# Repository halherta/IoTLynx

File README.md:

# IoTLynx

A maker-friendly ESP32-C6 development board designed for accessibility and ease of use.

## Overview

IoTLynx is a microcontroller development board based on Espressif's ESP32-C6 microcontroller (ESP32-C6-MINI-1 module). Designed with accessibility in mind, the IoTLynx platform caters to makers, hobbyists, and newcomers to programming and electronics. Though the board supports C programming, it was specifically designed to run MicroPython—a choice that aligns with its philosophy of ease of use. With the MicroPython REPL pre-loaded and ready to run, users can start coding immediately without the hassle of configuring development environments or installing IDEs.

## Features

### Hardware Specifications

**ESP32-C6 (ESP32-C6-MINI-1) Module:**
- **Processor:** RISC-V 32-bit single-core, up to 160 MHz
- **Memory:** 512 KB SRAM, 320 KB ROM, 4 MB embedded flash
- **Wireless:** Wi-Fi 6 (802.11 b/g/n, 2.4 GHz), Bluetooth 5.3 LE
- **GPIO:** 19 programmable GPIOs available on headers
- **Interfaces:** 2× SPI, 2× UART, 1× I2C, 1× I2S
- **Analog:** 7-channel 12-bit SAR ADC
- **PWM:** 6 LED PWM channels
- **USB:** USB 2.0 full-speed (OTG)
- **Other:** Built-in temperature sensor, 7-channel capacitive touch, hardware encryption

**Board Features:**
- **Dimensions:** 58mm × 38mm with rounded edges
- **Power Options:** USB-C or +5V via pin (can use both simultaneously)
- **Voltage Regulator:** Onboard +3.3V regulator
- **Headers:** 2× 14-pin female headers for GPIO access
- **Buttons:** RESET and BOOT pushbuttons
- **LED:** Power-on indicator
- **PCB:** 2-layer design with ground fills for noise immunity
- **Mounting:** M3 mounting holes on all four corners

### Power Consumption
- **Active mode (Wi-Fi):** ~95 mA
- **Modem-sleep:** ~15 mA
- **Light-sleep:** ~3 mA
- **Deep-sleep:** ~7-10 µA

## Pinout

Power can be applied via:
- **USB-C connector** for programming and power
- **+5Vin pin** (5V only) - can be used simultaneously with USB-C
- **+3V3 output** available for powering external components

## Schematic & PCB

The board features a straightforward design with all ESP32-C6-MINI-1 GPIOs (except USB pins) brought out to the headers. View the [full schematic PDF](https://github.com/halherta/IoTLynx/blob/main/IoTLynx.pdf) for complete details.

## Expansion Boards

The IoTLynx is designed to support "Top" boards—add-on boards that attach via the two female header connectors, similar to Arduino shields or Raspberry Pi hats. A KiCad template for creating Top boards is available in the [parts library](https://github.com/halherta/mykicadlibrary).

## Getting Started

### Prerequisites

- [Thonny IDE](https://thonny.org/) (MicroPython IDE)
- [esptool](https://github.com/espressif/esptool) (Espressif's flashing tool)
- [MicroPython firmware for ESP32-C6](https://micropython.org/download/ESP32_GENERIC_C6/)

### Installation

**1. Install Thonny and esptool:**

Via pip (in a Python virtual environment):
```bash
pip install thonny esptool
```

Or via apt (Debian/Ubuntu):
```bash
sudo apt install thonny esptool
```

**2. Find your serial port:**

Linux/Mac:
```bash
ls /dev/tty*
```

Windows (PowerShell):
```powershell
[System.IO.Ports.SerialPort]::getportnames()
```

Look for something like `/dev/ttyUSB0`, `/dev/ttyACM0` (Linux/Mac) or `COM3`, `COM4` (Windows).

**3. Erase the flash:**
```bash
esptool --chip esp32c6 --port /dev/ttyUSB0 erase_flash
```
*Replace `/dev/ttyUSB0` with your actual serial port.*

**4. Flash MicroPython firmware:**
```bash
esptool --chip esp32c6 --port /dev/ttyUSB0 write_flash -z 0x0 ESP32_GENERIC_C6-XXXXXXXX.bin
```
*Replace `ESP32_GENERIC_C6-XXXXXXXX.bin` with your downloaded firmware filename.*

**5. Configure Thonny:**
- Open Thonny
- Go to **Run → Configure Interpreter**
- Select **MicroPython (ESP32)** from the first dropdown
- Select your board's serial port from the second dropdown
- Click **OK**

You should see the MicroPython REPL prompt in the shell window:
```python
MicroPython v1.xx.x on 20xx-xx-xx; ESP32C6 module with ESP32C6
Type "help()" for more information.
>>>
```

Congratulations! You're ready to program your IoTLynx board!

## Repository Contents

- **IoTLynx.kicad_\*** - KiCad project files (schematic, PCB, settings)
- **IoTLynx.pdf** - Schematic in PDF format
- **IoTLynx.svg** - Board illustration
- **production/** - Manufacturing files (gerbers, BOM, etc.)
- **images/** - Documentation images
- **\*-backups/** - KiCad backup files

## Resources

- **Blog Post:** [Detailed IoTLynx writeup](https://hussamtalkstech.com/iotlynx/)
- **Parts Library:** [KiCad parts and Top board template](https://github.com/halherta/mykicadlibrary)
- **ESP32-C6 Datasheet:** [ESP32-C6-MINI-1 documentation](https://documentation.espressif.com/esp32-c6-mini-1_mini-1u_datasheet_en.html)
- **MicroPython Documentation:** [MicroPython for ESP32](https://docs.micropython.org/en/latest/esp32/quickref.html)

## License

This hardware project is open source. Please check the repository for specific license information.

## Contributing

Contributions, issues, and feature requests are welcome! Feel free to check the issues page or submit a pull request.

## Support

For questions, issues, or discussions about the IoTLynx board:
- Open an issue on this repository
- Visit the [blog post](https://hussamtalkstech.com/iotlynx/) for additional details

## Author

Created by [halherta](https://github.com/halherta)

---

**Note:** While the ESP32-C6 supports Zigbee, Thread, 6LoWPAN, and Matter protocols, these features are not currently available through MicroPython.

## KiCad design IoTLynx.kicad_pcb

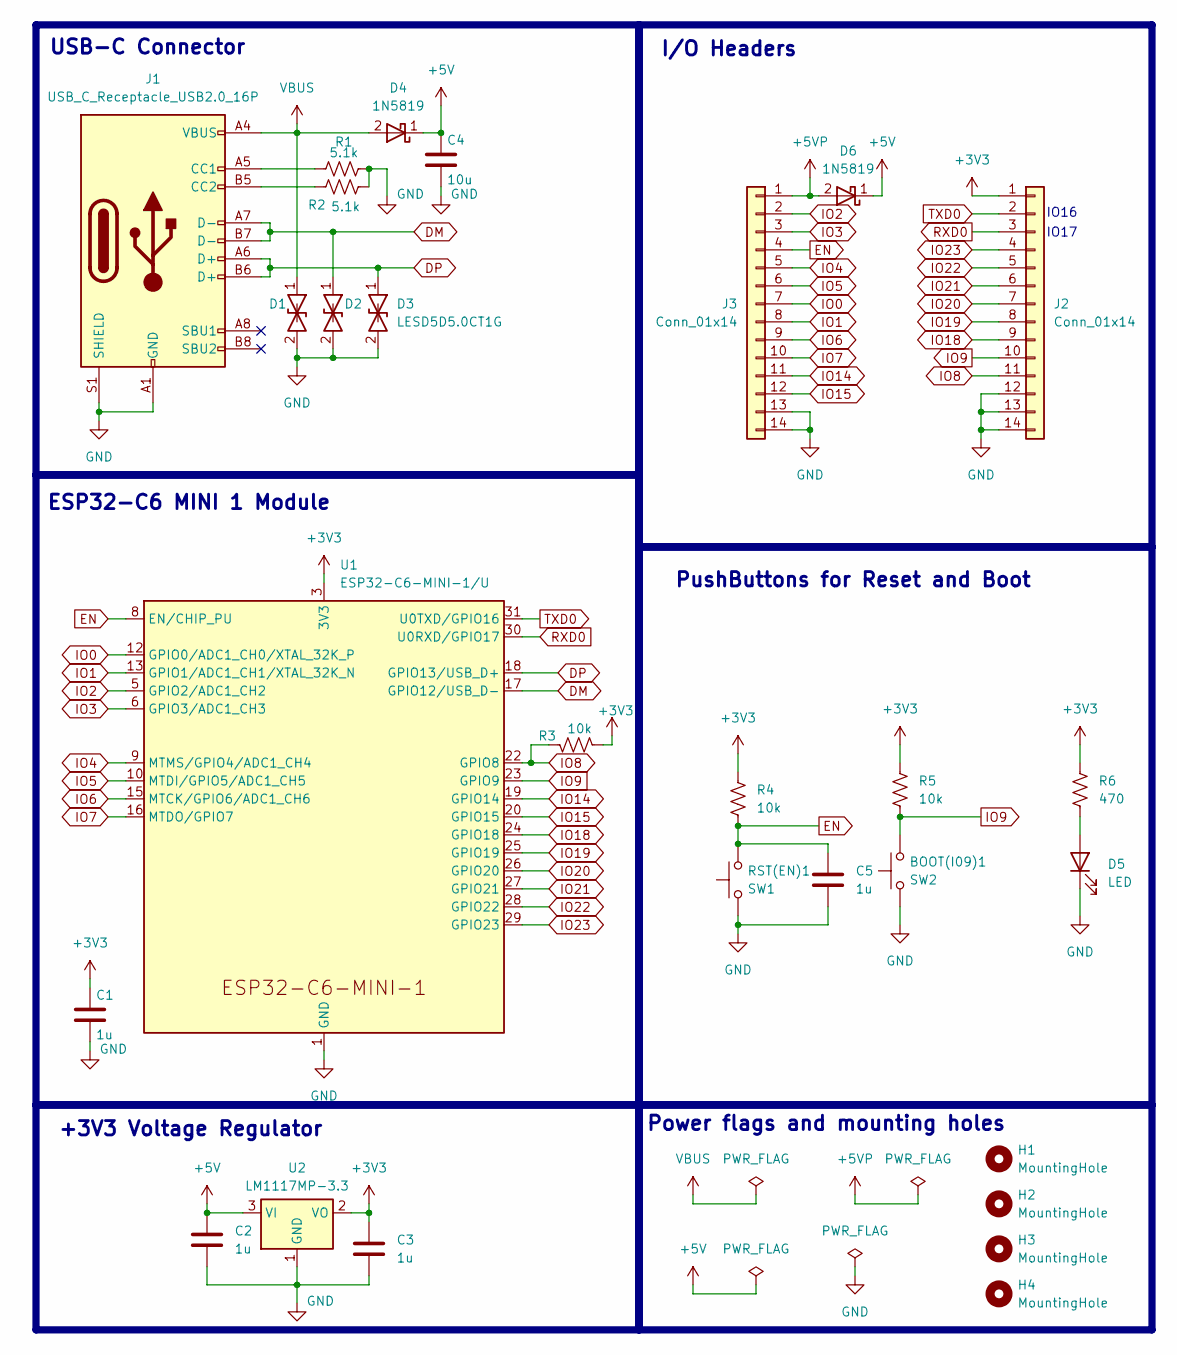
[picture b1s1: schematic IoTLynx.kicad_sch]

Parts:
BOOT(I09)1: SW2; SW_SPST_PTS810
C1, C2, C3: 1u; R_1206_3216Metric_Pad1.30x1.75mm_HandSolder
C4: 10u; R_1206_3216Metric_Pad1.30x1.75mm_HandSolder
C5: 1u; C_1206_3216Metric_Pad1.33x1.80mm_HandSolder
D1, D2, D3: LESD5D5.0CT1G; D_SOD-523
D4, D6: 1N5819; D_SOD-123
D5: LED; LED_1206_3216Metric_Pad1.42x1.75mm_HandSolder
H1, H2, H3, H4: MountingHole; MountingHole_3.2mm_M3
J1: USB_C_Receptacle_USB2.0_16P; USB_C_Receptacle_GCT_USB4110
J2, J3: Conn_01x14; PinSocket_1x14_P2.54mm_Vertical
R1, R2: 5.1k; R_1206_3216Metric_Pad1.30x1.75mm_HandSolder
R3, R4, R5: 10k; R_1206_3216Metric_Pad1.30x1.75mm_HandSolder
R6: 470; R_1206_3216Metric_Pad1.30x1.75mm_HandSolder
RST(EN)1: SW1; SW_SPST_PTS810
U1: ESP32-C6-MINI-1/U; ESP32-C6-MINI-1
U2: LM1117MP-3.3; SOT-223-3_TabPin2

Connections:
+3V3: C1.1, C3.1, J2.1, R3.2, R4.2, R5.2, R6.2, U1.3 (3V3), U2.2 (VO)
+5V: C2.1, C4.1, D4.1 (K), D6.1 (K), U2.3 (VI)
+5VP: D6.2 (A), J3.1
DM: D2.1 (A1), J1.A7 (D-), J1.B7 (D-), U1.17 (GPIO12/USB_D-)
DP: D3.1 (A1), J1.A6 (D+), J1.B6 (D+), U1.18 (GPIO13/USB_D+)
EN: C5.2, J3.4, R4.1, RST(EN)1.2, U1.8 (EN/CHIP_PU); also elsewhere on the board
GND: BOOT(I09)1.1, C1.2, C2.2, C3.2, C4.2, C5.1, D1.2 (A2), D2.2 (A2), D3.2 (A2), D5.1 (K), J1.A1 (GND), J1.A12 (GND), J1.B1 (GND), J1.B12 (GND), J1.S1 (SHIELD), J2.12, J2.13, J2.14, J3.13, J3.14, R1.2, R2.2, RST(EN)1.1, U1.1 (GND), U1.2 (GND), U1.11 (GND), U1.14 (GND), U1.36 (GND), U1.37 (GND), U1.38 (GND), U1.39 (GND), U1.40 (GND), U1.41 (GND), U1.42 (GND), U1.43 (GND), U1.44 (GND), U1.45 (GND), U1.46 (GND), U1.47 (GND), U1.48 (GND), U1.49 (GND), U1.50 (GND), U1.51 (GND), U1.52 (GND), U1.53 (GND), U2.1 (GND); also elsewhere on the board
IO0: J3.7, U1.12 (GPIO0/ADC1_CH0/XTAL_32K_P)
IO1: J3.8, U1.13 (GPIO1/ADC1_CH1/XTAL_32K_N)
IO2: J3.2, U1.5 (GPIO2/ADC1_CH2)
IO3: J3.3, U1.6 (GPIO3/ADC1_CH3)
IO4: J3.5, U1.9 (MTMS/GPIO4/ADC1_CH4)
IO5: J3.6, U1.10 (MTDI/GPIO5/ADC1_CH5)
IO6: J3.9, U1.15 (MTCK/GPIO6/ADC1_CH6)
IO7: J3.10, U1.16 (MTDO/GPIO7)
IO8: J2.11, R3.1, U1.22 (GPIO8)
IO9: BOOT(I09)1.2, J2.10, R5.1, U1.23 (GPIO9); also elsewhere on the board
IO14: J3.11, U1.19 (GPIO14)
IO15: J3.12, U1.20 (GPIO15)
IO18: J2.9, U1.24 (GPIO18)
IO19: J2.8, U1.25 (GPIO19)
IO20: J2.7, U1.26 (GPIO20)
IO21: J2.6, U1.27 (GPIO21)
IO22: J2.5, U1.28 (GPIO22)
IO23: J2.4, U1.29 (GPIO23)
unnamed: D5.2 (A), R6.1
unnamed: J1.A5 (CC1), R1.1
unnamed: J1.B5 (CC2), R2.1
RXD0: J2.3, U1.30 (U0RXD/GPIO17)
TXD0: J2.2, U1.31 (U0TXD/GPIO16)
VBUS: D1.1 (A1), D4.2 (A), J1.A4 (VBUS), J1.A9 (VBUS), J1.B4 (VBUS), J1.B9 (VBUS)

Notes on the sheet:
USB-C Connector
+3V3 Voltage Regulator
PushButtons for Reset and Boot
I/O Headers
Power flags and mounting holes
ESP32-C6 MINI 1 Module
IO17
IO16

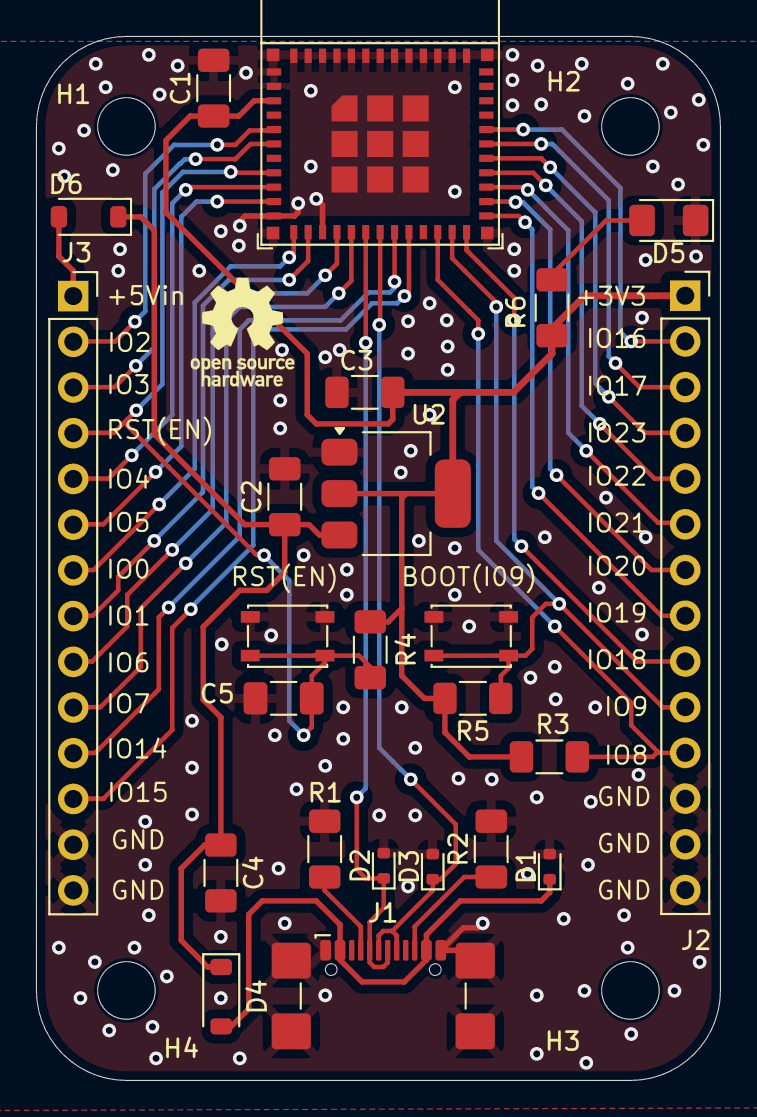
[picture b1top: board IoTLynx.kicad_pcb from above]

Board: 2 copper layers, 38.0 x 58.0 mm, 28 parts (0 on the bottom side), 31 nets.

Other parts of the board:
BOOT(I09): SW2; SW_SPST_PTS810
RST(EN): SW1; SW_SPST_PTS810

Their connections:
EN: RST(EN).2; also elsewhere on the board
GND: BOOT(I09).1, RST(EN).1; also elsewhere on the board
IO9: BOOT(I09).2; also elsewhere on the board

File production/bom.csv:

Designator,Footprint,Quantity,Value,LCSC Part #
BOOT(I09),SW_SPST_PTS810,1,SW2,
"C1, C2, C3, C5",1206,4,1u,
C4,1206,1,10u,
"D1, D2, D3",D_SOD-523,3,LESD5D5.0CT1G,
"D4, D6",D_SOD-123,2,1N5819,
D5,1206,1,LED,
J1,USB_C_Receptacle_GCT_USB4110,1,USB_C_Receptacle_USB2.0_16P,
"J2, J3",PinSocket_1x14_P2.54mm_Vertical,2,Conn_01x14,
"R1, R2",1206,2,5.1k,
"R3, R4, R5",1206,3,10k,
R6,1206,1,220,
RST(EN),SW_SPST_PTS810,1,SW1,
U1,ESP32-C6-MINI-1,1,ESP32-C6-MINI-1/U,
U2,SOT-223-3_TabPin2,1,LM1117MP-3.3,

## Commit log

2025-12-20 initial commit v2
2026-01-02 added some images and files
2026-01-02 added some images and files v2
2026-01-02 added some images and files v3
2026-01-02 added some images and files v4
2026-01-02 added some images and files v5
2026-01-03 added README
2026-01-03 resized photo
